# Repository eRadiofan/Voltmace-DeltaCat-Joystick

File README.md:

# Voltmace Delta-Cat Joystick Mouse Eliminator

This project documents the internals and functioning of this vintage Joystick for Acorn Archimedes computers.

Unlike earlier BBC micros, many of the Archimedes range did not include an analog port, so Voltmace came up with this solution, which plugs into the mouse port. It was a popular option for controlling FPV games, like Zarch, Chocks Away and Elite.

The back is held on with four screws, two shorter than the others. The top and bottom of the case form a clamp around the cable, so it takes a little effort to pull the back off.

Inside are the X/Y pots and a printed circuit board with (amongst other things) a quad OpAmp chip, 3 logic ICs and 2 PCB mounted pots used for controlling the vertial and horizontal speed.

The buttons are rubber membrane and pop off quite easily.

The circuit diagram is as follows:

The design is quite interesting. A positive voltage is supplied to the center of the X/Y poentiometers (via fixed resistors R7/R13) and each end of the pots are connected to ground via more resistors (R2/R6/R10/R16). The supply and ground resistors develop a small voltage across them but not enough to activate the rest of the circuit.

As the stick is moved in one direction, the drop in resistance across one side of the pot raises the voltage across some of these fixed resistors. The effects are two-fold:

1. The rise in potential across the ground resistor triggers a threshold detector (implemented by an OpAmp), indicating the direction of movement.
2. The rise in potential across the supply resistor activates a variable frequency oscillator (via transistor), that is otherwise idle. The greater the potential, the higher the frequency. The speed pots (RV3/RV4) affect the frequency range of the two oscillators.

The dead zone can be altered by adjusting R7/R13, increasing the value reduces the dead zone but beware that years of gaming introduces some play in the joystick column.

The output of the oscillator (U2A/U2F) goes into a delay gate (U2C/U2D), effectively producing the out-of-phase signal used for quadrature outputs. Both phase signals are then fed into a logic block (U3/U4) that passes them through unaltered if input is detected in one direction, or passes them reversed if input is detected in the opposite direction. The normally-high, low-going pulses are sent to the computer via the mouse port.

The PCB included in this project was intended to verify the circuit, by comparing it to the original. It is quite accurate dimensionally but the position of the speed pots might be off slightly and there are no pads for the rubber membrane keys (I have placed momenary switches instead). If you want to manufacture a PCB from this design, it will probably require a bit of tweaking. Using a modern microcontroller will probably be cheaper and the frequencies documented in the schematic should help.

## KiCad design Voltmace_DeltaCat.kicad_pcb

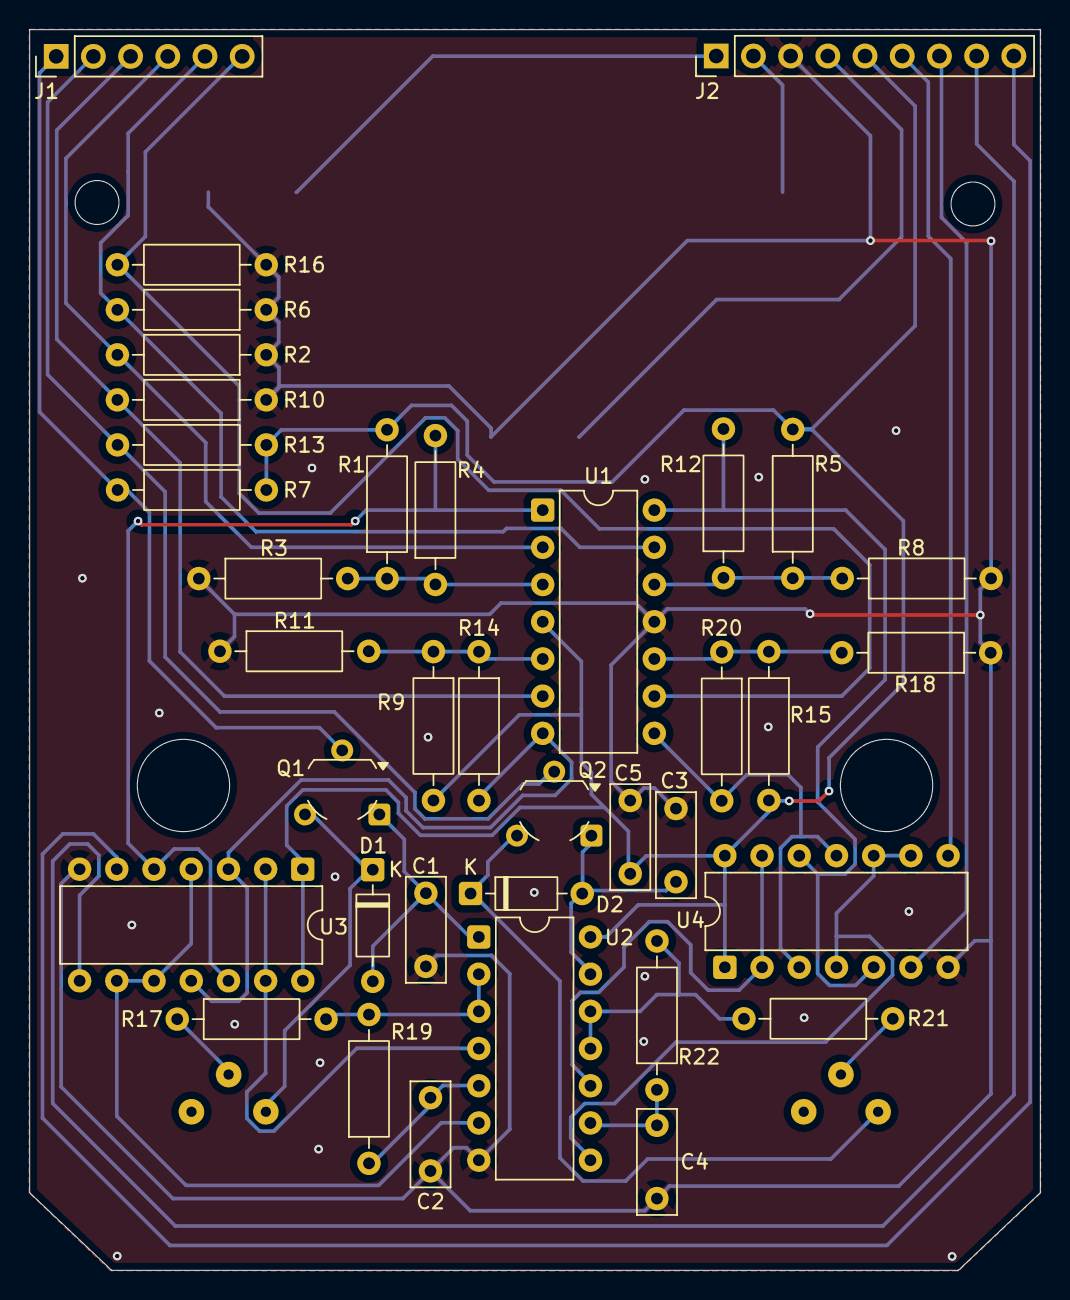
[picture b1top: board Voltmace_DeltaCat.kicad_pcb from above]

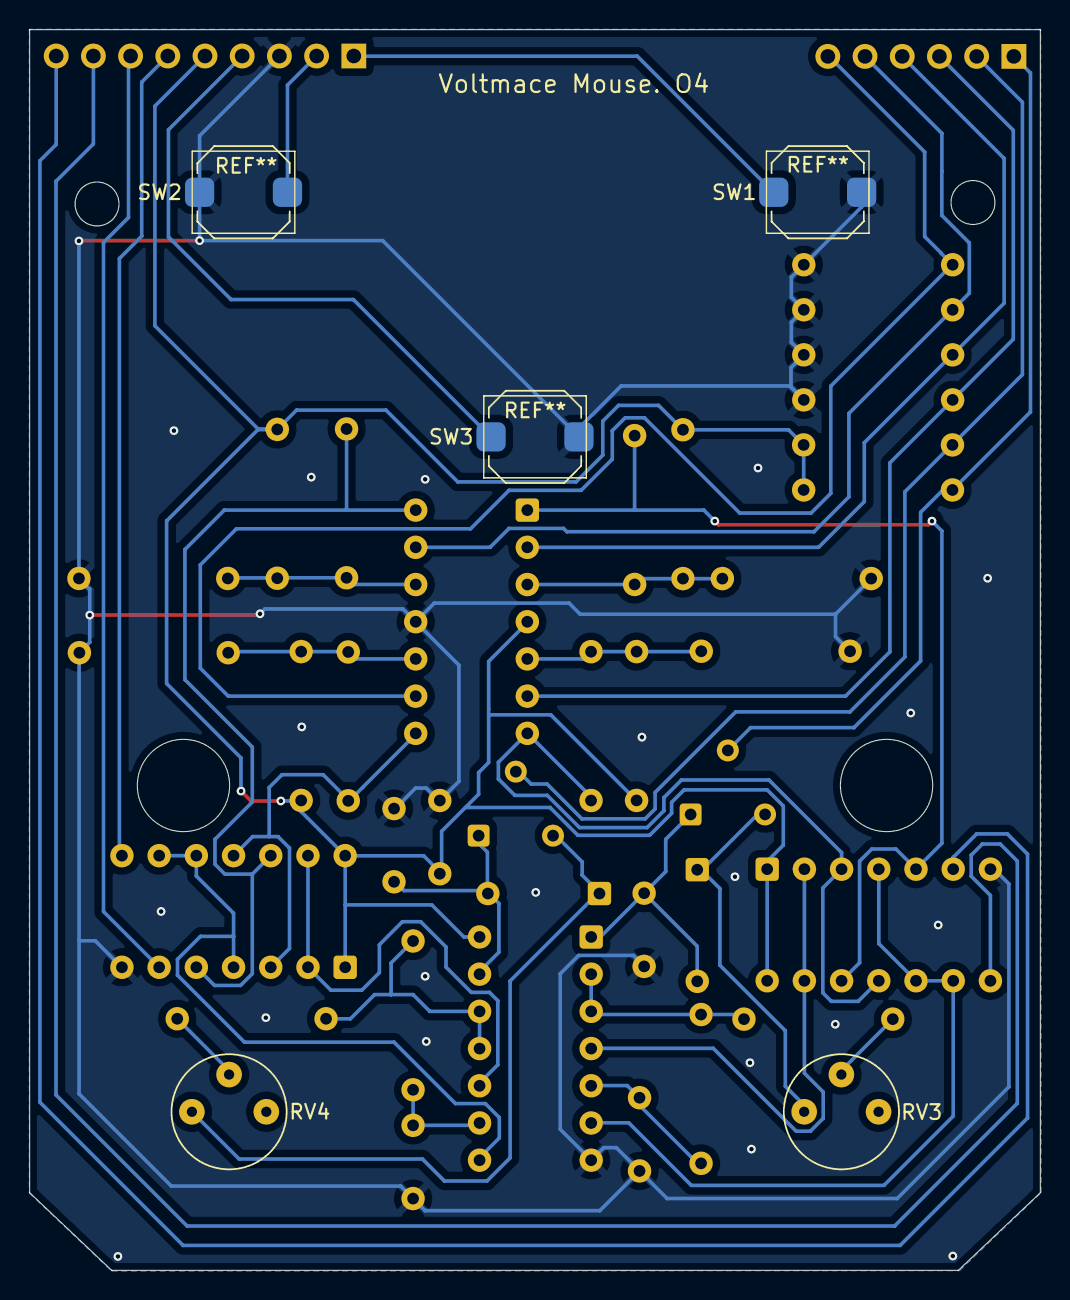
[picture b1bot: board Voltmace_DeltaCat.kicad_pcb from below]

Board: 2 copper layers, 69.0 x 84.7 mm, 42 parts (5 on the bottom side), 37 nets.

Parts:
C1, C2, C3, C4, C5: 0.1uF; C_Rect_L7.0mm_W2.5mm_P5.00mm
D1, D2: D; D_DO-35_SOD27_P7.62mm_Horizontal
J1: Conn_01x06; PinHeader_1x06_P2.54mm_Vertical
J2: Conn_01x09; PinHeader_1x09_P2.54mm_Vertical
Q1, Q2: BC558; TO-92_Custom
R1, R5, R9, R15: 27K; R_Axial_DIN0207_L6.3mm_D2.5mm_P10.16mm_Horizontal
R2, R6, R10, R16, R17, R21: 10K; R_Axial_DIN0207_L6.3mm_D2.5mm_P10.16mm_Horizontal
R3, R7, R8, R11, R13, R18, R19, R22: 3K; R_Axial_DIN0207_L6.3mm_D2.5mm_P10.16mm_Horizontal
R4, R12: 270K; R_Axial_DIN0207_L6.3mm_D2.5mm_P10.16mm_Horizontal
R14, R20: 330K; R_Axial_DIN0207_L6.3mm_D2.5mm_P10.16mm_Horizontal
RV3, RV4: 50K; Potentiometer_Bourns_3339P_Vertical_HandSoldering
SW1, SW2, SW3: SW_SPST; SW_Push_1TS009xxxx-xxxx-xxxx_6x6x5mm
U1: CA324; DIP-14_W7.62mm
U2: 74HC14; DIP-14_W7.62mm
U3: 74HC51; DIP-14_W7.62mm
U4: 74LS51; DIP-14_W7.62mm

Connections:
/CK_H: U2.10, U4.2, U4.13
/CK_V: U2.4, U3.2, U3.13
/DIR_DWN: R14.2, U1.7, U3.3, U3.11
/DIR_LEFT: R20.2, U1.8, U4.3, U4.11
/DIR_RIGHT: R12.2, U1.14, U4.5, U4.12
/DIR_UP: R4.2, U1.1, U3.5, U3.12
/H_A: J2.7, U4.6
/H_B: J2.6, U4.8
/V_A: J2.9, U3.6
/V_B: J2.8, U3.8
/nCK_H: U2.8, U4.4, U4.9, U4.10
/nCK_V: U2.6, U3.4, U3.9, U3.10
GND: C1.2, C2.2, C3.2, C4.2, C5.2, J2.3, R2.1, R3.1, R6.1, R8.1, R10.1, R11.1, R16.1, R18.1, SW1.1 (A), SW2.1 (A), SW3.1 (A), U1.11 (V-), U2.7 (GND), U3.7 (GND), U4.7 (GND)
unnamed: C2.1, R19.1, U2.5
unnamed: C4.1, R22.1, U2.9
unnamed: C1.1, D1.2 (A), Q1.1 (C), U2.1
unnamed: D1.1 (K), Q1.3 (E), RV3.1
unnamed: C3.1, D2.2 (A), Q2.1 (C), U2.13
unnamed: D2.1 (K), Q2.3 (E), RV4.1
unnamed: J1.1, Q1.2 (B), R7.1
unnamed: J1.2, Q2.2 (B), R13.1
unnamed: J1.3, R10.2, U1.6 (-)
unnamed: J1.4, R2.2, U1.2 (-)
unnamed: J1.5, R6.2, U1.13 (-)
unnamed: J1.6, R16.2, U1.9 (-)
unnamed: J2.1, SW1.2 (B)
unnamed: J2.2, SW2.2 (B)
unnamed: J2.4, SW3.2 (B)
unnamed: R17.1, RV3.2
unnamed: R17.2, R19.2, U2.2, U2.3
unnamed: R21.1, RV4.2
unnamed: R21.2, R22.2, U2.11, U2.12
unnamed: R1.1, R3.2, R4.1, U1.3 (+)
unnamed: R9.1, R11.2, R14.1, U1.5 (+)
unnamed: R15.1, R18.2, R20.1, U1.10 (+)
unnamed: R5.1, R8.2, R12.1, U1.12 (+)
VCC: C5.1, J2.5, R1.2, R5.2, R7.2, R9.2, R13.2, R15.2, U1.4 (V+), U2.14 (VCC), U3.1, U3.14 (VCC), U4.1, U4.14 (VCC)
